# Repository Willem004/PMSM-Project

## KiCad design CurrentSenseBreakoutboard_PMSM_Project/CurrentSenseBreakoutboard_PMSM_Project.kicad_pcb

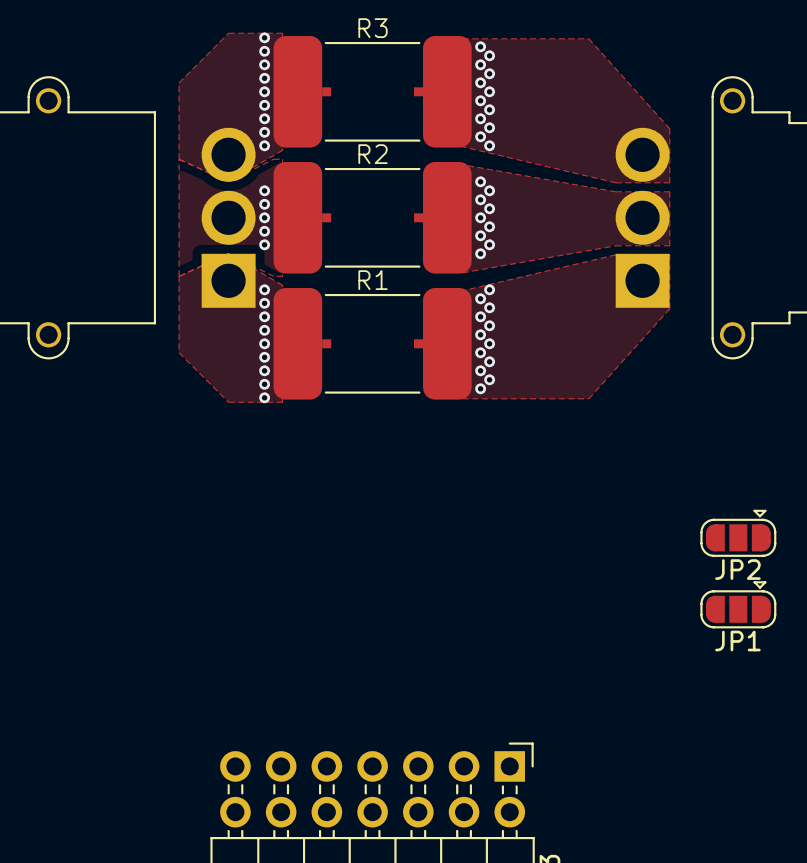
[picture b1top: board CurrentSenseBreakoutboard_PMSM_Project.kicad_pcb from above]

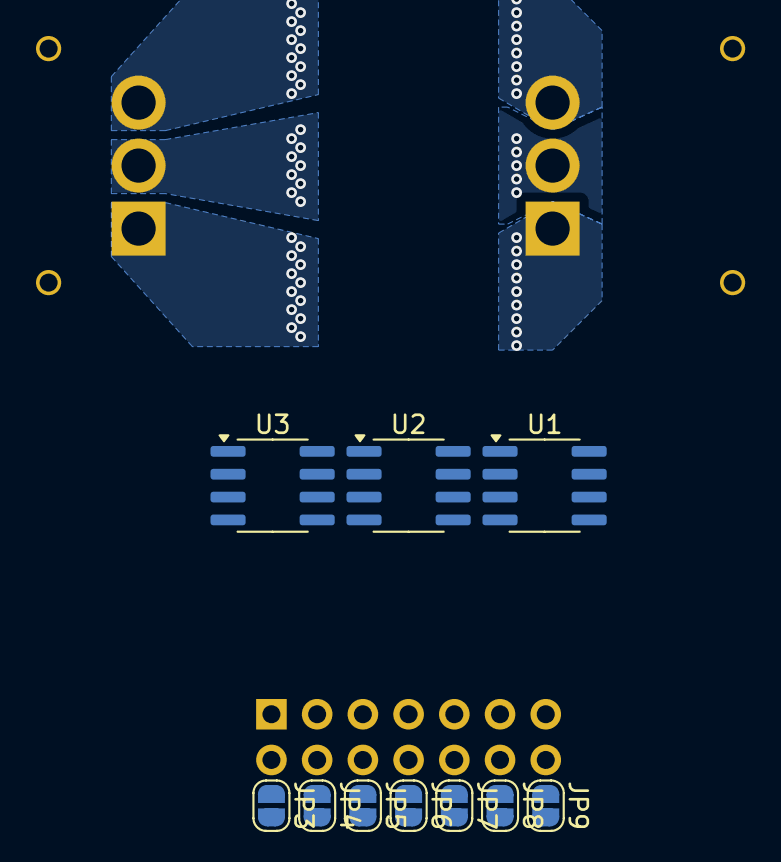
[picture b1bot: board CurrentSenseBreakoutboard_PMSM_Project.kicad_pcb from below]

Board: 2 copper layers, 18 parts (10 on the bottom side), 28 nets, no tracks yet.

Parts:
J1: MR30PW-M; AMASS_MR30PW-M_1x03_P3.50mm_Horizontal
J2: MR30PW-FB; AMASS_MR30PW-FB_1x03_P3.50mm_Horizontal
J3: Conn_02x07_Odd_Even; PinHeader_2x07_P2.54mm_Horizontal
JP1, JP2: SolderJumper_3_Open; SolderJumper-3_P1.3mm_Open_RoundedPad1.0x1.5mm
JP3, JP4, JP5, JP6, JP7, JP8, JP9: SolderJumper_2_Open; SolderJumper-2_P1.3mm_Open_RoundedPad1.0x1.5mm
R1, R2, R3: EWSL3920F1L50Q9; R_Shunt_3920_10052Metric
U1, U2, U3: INA240A1D; SOIC-8_3.9x4.9mm_P1.27mm

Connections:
IN_U: J1.1, R1.1
IN_V: J1.2, R2.1
IN_W: J1.3, R3.1
I_U_OUT: J3.1, U1.5
I_V_OUT: J3.3, U2.5
I_W_OUT: J3.5, U3.5
unnamed: J3.2, JP3.1 (A)
unnamed: J3.4, JP4.1 (A)
unnamed: J3.6, JP5.1 (A)
unnamed: J3.8, JP6.1 (A)
unnamed: J3.10, JP7.1 (A)
unnamed: J3.12, JP8.1 (A)
unnamed: J3.14, JP9.1 (A)
unnamed: R1.2, U1.8 (+)
unnamed: R1.3, U1.1 (-)
unnamed: R2.2, U2.8 (+)
unnamed: R2.3, U2.1 (-)
unnamed: R3.2, U3.8 (+)
unnamed: R3.3, U3.1 (-)
OUT_U: J2.1, R1.4
OUT_V: J2.2, R2.4
OUT_W: J2.3, R3.4
REF1: JP2.2 (C), U1.7 (REF1), U2.7 (REF1), U3.7 (REF1)
REF1_IN: J3.7, JP2.3 (B)
REF2: JP1.2 (C), U1.3 (REF2), U2.3 (REF2), U3.3 (REF2)
REF2_IN: J3.9, JP1.3 (B)
VDD: J3.13, JP1.1 (A), U1.6 (V+), U2.6 (V+), U3.6 (V+)
VSS: J3.11, JP2.1 (A), JP3.2 (B), JP4.2 (B), JP5.2 (B), JP6.2 (B), JP7.2 (B), JP8.2 (B), JP9.2 (B), U1.2 (GND), U1.4 (GND), U2.2 (GND), U2.4 (GND), U3.2 (GND), U3.4 (GND)

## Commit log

2024-10-17 moved existing files to the repository
2024-10-17 forgot these
2025-02-11 Added DC in and 3 Phase out connectors to the schematic
2025-02-11 a bunch of defaults changed by opening the project with kicad
2025-02-11 added .lck files to gitignore
2025-02-11 Create #auto_saved_files#
2025-02-11 Added datasheets of amass connectors
